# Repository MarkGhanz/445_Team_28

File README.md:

# 445_Team_28
Github repo of the code used

## ATTENTION
The final version of the base station is in the folder `base_station`.<br>
The final version of the sensor-transmitter-combinations is in the folder `sensor_tx`. <br>
The PCB design for the base station is in the folder `445_project`.<br>

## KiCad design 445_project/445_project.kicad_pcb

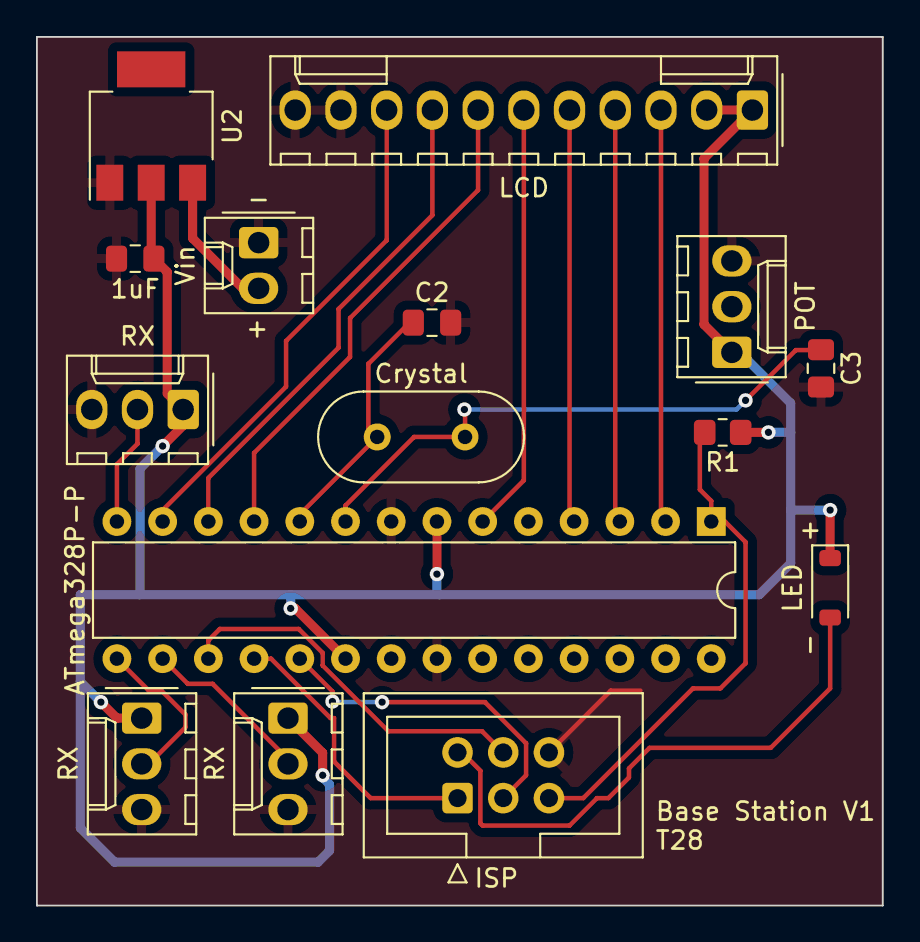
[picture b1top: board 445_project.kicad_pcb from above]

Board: 2 copper layers, 47.0 x 48.3 mm, 15 parts (0 on the bottom side), 20 nets.

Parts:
C1: 1uF; C_0805_2012Metric_Pad1.18x1.45mm_HandSolder
C2, C3: 22P; C_0805_2012Metric_Pad1.18x1.45mm_HandSolder
D1: LED; D_SOD-123
J1: Vin; Molex_KK-254_AE-6410-02A_1x02_P2.54mm_Vertical
J2: ISP; IDC-Header_2x03_P2.54mm_Vertical
LCD1: LCD; Molex_KK-254_AE-6410-11A_1x11_P2.54mm_Vertical
POT1: POT; Molex_KK-254_AE-6410-03A_1x03_P2.54mm_Vertical
R1: 10k; R_0805_2012Metric_Pad1.20x1.40mm_HandSolder
RX_1, RX_2, RX_3: RX; Molex_KK-254_AE-6410-03A_1x03_P2.54mm_Vertical
U1: ATmega328P-P; DIP-28_W7.62mm
U2: U2; SOT-223
Y1: Crystal; Crystal_HC49-4H_Vertical

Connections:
+5V: C1.2, D1.1 (K), LCD1.1, LCD1.2, POT1.1, R1.1, RX_1.1, RX_2.1, RX_3.1, U1.7 (VCC), U1.20 (AVCC), U2.2 (VO)
/D1: RX_1.2, U1.14 (PB0)
/D2: RX_2.2, U1.15 (PB1)
/D3: RX_3.2, U1.16 (PB2)
/DB4: LCD1.6, U1.6 (PD4)
/DB5: LCD1.7, U1.11 (PD5)
/DB6: LCD1.8, U1.12 (PD6)
/DB7: LCD1.9, U1.13 (PD7)
/E: LCD1.3, U1.2 (PD0)
/MISO: J2.1 (MISO), U1.18 (PB4)
/MOSI: J2.4 (MOSI), U1.17 (PB3)
/RS: LCD1.5, U1.4 (PD2)
/RST: J2.5 (~RST), R1.2, U1.1 (~RESET/PC6)
/RW: LCD1.4, U1.3 (PD1)
/SCK: J2.3 (SCK), U1.19 (PB5)
GND: C1.1, C2.2, C3.2, J1.1, J2.6 (GND), LCD1.10, LCD1.11, POT1.3, RX_1.3, RX_2.3, RX_3.3, U1.8 (GND), U1.22 (GND), U2.1 (GND)
unnamed: D1.2 (A), J2.2 (VCC)
unnamed: J1.2, U2.3 (VI)
unnamed: C3.1, U1.9 (XTAL1/PB6), Y1.1
unnamed: C2.1, U1.10 (XTAL2/PB7), Y1.2

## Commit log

2023-12-07 uploading the files used
